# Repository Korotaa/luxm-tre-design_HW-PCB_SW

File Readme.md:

# TSL25711 sensor with LoRa module and ESP32 chip 

## Bloc Diagramm

Le module est un End Device LoRa. C'est un dispositif IoT permettant de mesurer le niveau de luminosité grace au capteur TSL2571 et transmettre ces données à un serveur LoRaWAN (NetWork Serveur + Application Serveur) . Il peut recevoir des informations de commandes downlink de l'utilisateur.

- RF-LORA-868-SO : Transceiver LoRa pour la transmission et la reception de données sans fils. Il communique avec le MCU via une interface SPI. MISO_L pour l'envoie de données du transceiver vers le MCU et MOSI_L pour l'envoie des données du MCU vers le transceiver.
- TSL25711 : Dispositif sensible à la lumière ambiante. La valeur de sortie du capteur est transférée au MCU via l'interface I2C. Le MCU determine la valeur en LUX du rayonnement lumineux grace à une formule empirique. On retrouve le capteur dans les écrans de pc ou des smartphones. L'objectif est afin d’adapter l’intensité lumineuse émise par l’écran à la lumière ambiante, l’objectif étant de réduire la consommation de l’écran qui peut représenter jusqu’à 40% de l’énergie consommée.  
- MCU est un ESP32 
- Le dispositif possède 3 modes d'alimentations : USB, battery, ou par une alimentation externe. Lorsque le module est alimentée par USB, la batterie est chargée par la même occasion via le circuit MCP73831. 
- Il existe plusieurs points de tests permettant de visualiser grâce un oscilloscope les trames LoRa, la consommation de la carte etc...
- Le End Device est utilisé pour adapter l'éclairement d'un laboratoire en fonction de la lumière ambiante. 

- Le firmware est dévéloppé avec ESP-IDF. 

## PCB

<!--  -->

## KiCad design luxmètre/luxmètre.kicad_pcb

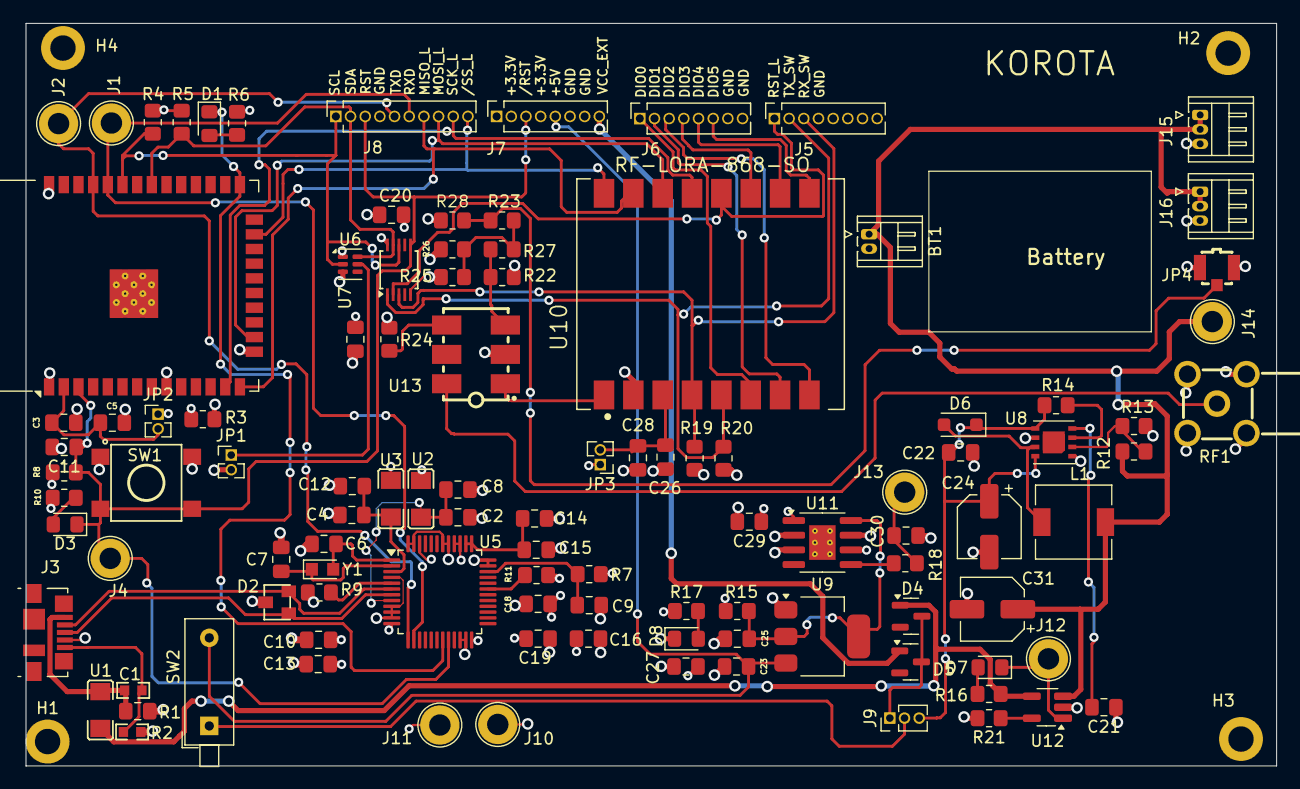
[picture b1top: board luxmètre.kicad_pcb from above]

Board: 4 copper layers, 108.2 x 64.2 mm, 110 parts (0 on the bottom side), 62 nets.

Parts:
BT1: Battery; Hirose_DF13-02P-1.25DS_1x02_P1.25mm_Horizontal
C1, C2, C4, C5, C23, C25, C28: 10uF; C_0805_2012Metric_Pad1.18x1.45mm_HandSolder
C3, C8, C10, C11, C12, C13, C15, C16, C17, C18, C19, C20, C21, C22, C26, C27, C29: 100nF; C_0805_2012Metric_Pad1.18x1.45mm_HandSolder
C6, C7, C9, C30: 10nF; C_0805_2012Metric_Pad1.18x1.45mm_HandSolder
C14: 3.3uF; C_0805_2012Metric_Pad1.18x1.45mm_HandSolder
C24, C31: 47uF; CP_Elec_5x5.4
D1, D3, D7, D8: LED; LED_0805_2012Metric_Pad1.15x1.40mm_HandSolder
D2: PGB102ST23WR; SOT-23_L3.0-W2.2-P0.95-LS2.2-TR
D4, D5: BAT54C; SOT-23
D6: MBR0520LT; D_SOD-123F
H1, H2, H3, H4: MountingHole; MountingHole_2.2mm_M2_DIN965_Pad
J1, J2, J4, J10, J11, J12, J13, J14: Conn_01x01; TestPoint_Loop_D2.50mm_Drill1.85mm
J3: USB_A; USB_Micro-B_Molex_47346-0001
J5: Conn_01x04; PinSocket_1x08_P1.27mm_Vertical
J6, J7: Conn_01x08; PinSocket_1x08_P1.27mm_Vertical
J8: Conn_01x10; PinSocket_1x10_P1.27mm_Vertical
J9: Conn_01x03; PinHeader_1x03_P1.27mm_Vertical
J15, J16: Conn_01x03; Hirose_DF13-03P-1.25DS_1x03_P1.25mm_Horizontal
JP1, JP2, JP3: Jumper_2_Open; PinHeader_1x02_P1.27mm_Vertical
JP4: U.FL-R-SMT-1(80); RF-SMD_FRF05002-JSS103M
L1: 22uH; L_6.3x6.3_H3
R1, R2: V5.5MLA0603NH; R0603
R3, R7, R8, R9: 10k; R_0805_2012Metric_Pad1.20x1.40mm_HandSolder
R4, R5: 4k7; R_0805_2012Metric_Pad1.20x1.40mm_HandSolder
R6, R10: 470R; R_0805_2012Metric_Pad1.20x1.40mm_HandSolder
R11: 47k; R_0805_2012Metric_Pad1.20x1.40mm_HandSolder
R12: 113k; R_0805_2012Metric_Pad1.20x1.40mm_HandSolder
R13, R14, R19, R20: 100k; R_0805_2012Metric_Pad1.20x1.40mm_HandSolder
R15: 0R1; R_0805_2012Metric_Pad1.20x1.40mm_HandSolder
R16: 1.5k; R_0805_2012Metric_Pad1.20x1.40mm_HandSolder
R17, R18: 330R; R_0805_2012Metric_Pad1.20x1.40mm_HandSolder
R21: 2k; R_0805_2012Metric_Pad1.20x1.40mm_HandSolder
R22, R25, R26, R28: 68R; R_0805_2012Metric_Pad1.20x1.40mm_HandSolder
R23, R27: 270R; R_0805_2012Metric_Pad1.20x1.40mm_HandSolder
R24: R; R_0805_2012Metric_Pad1.20x1.40mm_HandSolder
RF1: HJ-SMA313; SMA-TH_HJ-2LC15SF048
SW1: B3S-1000P; KEY-SMD_4P-L6.6-W6.0-P4.50-LS9.0-BR
SW2: SW_DIP_x01; SW_DIP_SPSTx01_Piano_10.8x4.1mm_W7.62mm_P2.54mm
U1, U2, U3: ILB1206ER260V; L1206
U4: ESP32-WROOM-32
U5: FT232HL; LQFP-48_7x7mm_P0.5mm
U6: AMS_TSL25911FN
U7: PCA9537DP; TSSOP-10_3x3mm_P0.5mm
U8: MAX1674EUA+T; Converter_DCDC_Cyntec_MUN12AD01-SH
U9: LM1117MP-3.3; SOT-223-3_TabPin2
U10: RF-LORA-868-SO; XCVR_RF-LORA-868-SO
U11: AD8418; SOIC-8-1EP_3.9x4.9mm_P1.27mm_EP2.29x3mm_ThermalVias
U12: MCP73831-2-MC; SOT-23-5_HandSoldering
U13: ADC-10-4+; XFMR-SMD_6P-L7.9-W5.6-P2.54-LS7.0-BL
Y1: 12MHz; Crystal_SMD_2012-2Pin_2.0x1.2mm_HandSoldering

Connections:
5V_BAT: C22.2, C24.1, D6.1 (K), J9.3, R14.1, U8.5 (~SHDN), U8.8 (OUT)
+3.3V: C10.1, C13.2, C16.1, C17.1, C18.2, C19.1, C20.1, C27.1, C29.1, J7.2, J7.4, J11.1, JP2.1 (A), JP3.1 (A), R3.1, R4.1, R5.1, R6.1, R7.1, R8.1, R10.1, R11.2, R15.2, R17.1, U2.1, U3.1, U5.12 (VCCIO), U5.24 (VCCIO), U5.39 (VCCD), U5.40 (VREGIN), U5.46 (VCCIO), U6.1 (VDD), U7.10 (VDD), U11.1 (IN-), U11.6 (VS)
+5V: C23.1, J7.5, SW2.2, U9.3 (VI)
/5V_usb: C1.1, J3.1 (VBUS), R1.2, U1.1
/ANT: U10.1 (ANT), U13.1 (INPUT)
/BOOT: D1.1 (K), U4.25 (IO0), U5.19 (ADBUS6)
/C: R22.2, R23.1, U13.3 (COUPLED)
/DIO0: J6.1, U10.6 (DIO0)
/DIO1: J6.2, U10.7 (DIO1)
/DIO2: J6.3, U10.8 (DIO2)
/DIO3: J6.4, U10.11 (DIO5)
/DIO4: J6.5, U10.10 (DIO4)
/DIO5: J6.6, U10.9 (DIO3)
/IRQ_Lum: JP1.1 (A), U6.5 (INT)
/MISO_L: J8.7, U4.14 (IO12), U10.15 (SDI)
/MOSI_L: J8.8, U4.16 (IO13), U10.14 (SDO)
/RST: C11.1, D3.1 (K), J4.1, J7.3, J8.3, R8.2, SW1.3, SW1.4, U4.3 (EN), U5.20 (ADBUS7), U7.6 (RESET/)
/RST_L: J5.1, U7.2 (IO0), U10.12 (RESET)
/RXD: J1.1, J8.6, U4.34 (RXD0/IO3), U5.14 (ADBUS1)
/RX_SW: J5.3, R19.2, U7.3 (IO2), U10.4 (RX_SWITCH)
/SCK_L: J8.9, U4.13 (IO14), U10.13 (SCLK)
/SCL: J8.1, R4.2, U4.33 (IO21), U6.2 (SCL), U7.8 (SCL)
/SDA: J8.2, R5.2, U4.31 (IO19), U6.6 (SDA), U7.9 (SDA)
/TXD: J2.1, J8.5, U4.35 (TXD0/IO1), U5.13 (ADBUS0)
/TX_SW: J5.2, R20.2, U7.1 (IO1), U10.5 (TX_SWITCH)
/dm: D2.2, J3.2 (D-), U5.6 (DM)
/dp: D2.1, J3.3 (D+), U5.7 (DP)
//SS_L: J8.10, U4.23 (IO15), U10.16 (~SEL)
GND: BT1.2 (-), C1.2, C2.2, C3.2, C4.2, C5.2, C6.2, C7.2, C8.2, C9.2, C10.2, C11.2, C12.1, C13.1, C14.2, C15.2, C16.2, C17.2, C18.1, C19.2, C20.2, C21.1, C22.1, C23.2, C24.2, C25.2, C26.2, C27.2, C28.2, C29.2, C30.2, C31.2, D2.3, D8.1 (K), J3.4 (GND), J5.4, J6.7, J6.8, J7.6, J7.7, J8.4, J10.1, J15.3, J16.3, JP1.2 (B), JP4.2 (GND), JP4.3 (GND), R2.2, R3.2, R9.1, R13.1, R19.1, R20.1, R21.2, R22.1, R24.1, R25.1, R26.1, R28.1, RF1.2, RF1.3, RF1.4, RF1.5, SW1.1, SW1.2, U4.1 (GND), U4.9 (IO33), U4.15 (GND), U4.38 (GND), U4.39 (GND), U5.4 (AGND), U5.9 (AGND), U5.10 (GND), U5.11 (GND), U5.22 (GND), U5.23 (GND), U5.35 (GND), U5.36 (GND), U5.41 (AGND), U5.42 (TEST), U5.47 (GND), U5.48 (GND), U6.3 (GND), U7.5 (VSS), U8.1 (FB), U8.6 (GND), U9.1 (GND), U10.2 (GND), U11.2 (GND), U11.3 (REF2), U11.7 (REF1), U12.2 (V_{SS}), U13.2 (GROUND)
GNDPWR: J3.5 (Shield), R1.1, R2.1
unnamed: D1.2 (A), R6.2
unnamed: D3.2 (A), R10.2
unnamed: D6.2 (A), L1.2, U8.7 (LX)
unnamed: D7.2 (A), R16.2
unnamed: D7.1 (K), J12.1, U12.1 (STAT)
unnamed: D8.2 (A), R17.2
unnamed: D4.3, D5.3, J9.1
unnamed: J9.2, SW2.1
unnamed: C30.1, J13.1, R18.2
unnamed: C3.1, C5.1, JP2.2 (B), U4.2 (VDD)
unnamed: C26.1, C28.1, JP3.2 (B), U10.3 (VCC)
unnamed: JP4.1 (SIG), R27.2, R28.2
unnamed: R23.2, R25.2, R26.2, R27.1
unnamed: R11.1, U5.31 (ACBUS7)
unnamed: R9.2, U5.5 (REF)
unnamed: C14.1, C15.1, U5.37 (VCCA), U5.38 (VCORE)
unnamed: C4.1, C12.2, U3.2, U5.3 (VPHY)
unnamed: C2.1, C8.1, U2.2, U5.8 (VPLL)
unnamed: C6.1, U5.1 (XCSI), Y1.2
unnamed: C7.1, U5.2 (XCSO), Y1.1
unnamed: C9.1, R7.2, U5.34 (~RESET)
unnamed: R12.1, R13.2, U8.2 (LBI)
unnamed: C21.2, U8.4 (REF)
unnamed: R14.2, U8.3 (~LBO)
unnamed: C25.1, R15.1, U9.2 (VO), U11.8 (IN+)
unnamed: R18.1, U11.5 (OUT)
unnamed: R21.1, U12.5 (PROG)
unnamed: RF1.1, U13.6 (OUTPUT)
unnamed: R24.2, U13.4 (TERM)
VCC_EXT: D5.1, J7.8
VCC_USB: D4.1, R16.1, U1.2, U12.4 (V_{DD})
V_BAT: BT1.1 (+), C31.1, J14.1, J15.1, J15.2, J16.1, J16.2, L1.1, R12.2, U12.3 (V_{BAT})

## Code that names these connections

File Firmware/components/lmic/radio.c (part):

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    // configure output power
    configPower();

    // set the IRQ mapping DIO0=PacketSent DIO1=NOP DIO2=NOP
    writeReg(RegDioMapping1, MAP_DIO0_FSK_READY|MAP_DIO1_FSK_NOP|MAP_DIO2_FSK_TXNOP);

    // initialize the payload size and address pointers
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    // set sync word
    writeReg(LORARegSyncWord, LORA_MAC_PREAMBLE);

    // set the IRQ mapping DIO0=TxDone DIO1=NOP DIO2=NOP
    writeReg(RegDioMapping1, MAP_DIO0_LORA_TXDONE|MAP_DIO1_LORA_NOP|MAP_DIO2_LORA_NOP);
    // clear all radio IRQ flags
    writeReg(LORARegIrqFlags, 0xFF);
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    // set sync word
    writeReg(LORARegSyncWord, LORA_MAC_PREAMBLE);

    // configure DIO mapping DIO0=RxDone DIO1=RxTout DIO2=NOP
    writeReg(RegDioMapping1, MAP_DIO0_LORA_RXDONE|MAP_DIO1_LORA_RXTOUT|MAP_DIO2_LORA_NOP);
    // clear all radio IRQ flags
    writeReg(LORARegIrqFlags, 0xFF);
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    writeReg(FSKRegFdevMsb, 0x01); // +/- 25kHz
    writeReg(FSKRegFdevLsb, 0x99);

    // configure DIO mapping DIO0=PayloadReady DIO1=NOP DIO2=TimeOut
    writeReg(RegDioMapping1, MAP_DIO0_FSK_READY|MAP_DIO1_FSK_NOP|MAP_DIO2_FSK_TIMEOUT);

    // enable antenna switch for RX
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
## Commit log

2024-09-16 routage computing unit bloc
2024-10-03 firmware

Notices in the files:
Firmware/components/lmic/radio.c:
Copyright (c) 2014-2016 IBM Corporation.
All rights reserved.
